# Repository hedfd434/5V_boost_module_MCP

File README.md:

# 5V converter evaluation board (MCP1640T-I/CHY)
this board allows user to get 5V power supply with maximum out current of 1A (limited by coil to 0.8A).
You can safely power your 5V devices controlled by MCU's or evaluation boards

<figure>

  <figcaption>
    Image 1 and 2. Board in real usage power 5V servo
  </figcaption>
</figure>

## features
- DC to DC power conversion (boost)
- input voltage 3.0 to 4.2 V (possible change to range of 0.9 to 1.7V by replacing 309ohm resistor with 562ohm resistor)
- up to 95% efficiency in range of 10 - 100mA
- custom enabler: you can control on and off state by EN pin or permanently solder the 0ohm resistor.

<figure>

  <figcaption>
    Image 3 and 4. Detailed view with real scale.
  </figcaption>
</figure>

## issues
- the GPIO pins are not alligned, it requires using 2 bread boards or custom cutouts in pcb.

## components used in the project
1. 5V chip MCP1640T-I/CHY
2. coil LQM21PN4R7MGRD
3. 10uF 0603 capacitor
4. 4.7uG 0603 capacitor
4. 0ohm 0603 resitor
5. 309ohm 0603 resistor
6. 976ohm 0603 resistor

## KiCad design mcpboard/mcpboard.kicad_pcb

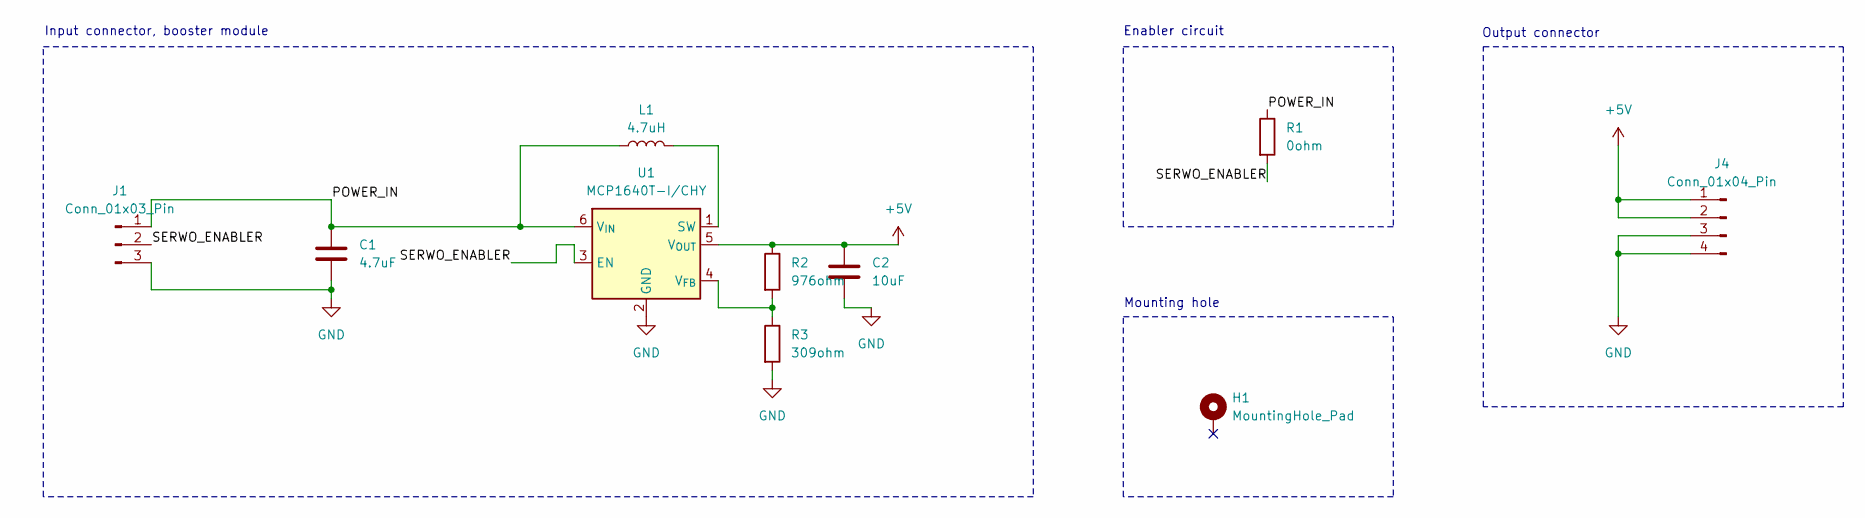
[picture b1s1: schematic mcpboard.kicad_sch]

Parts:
C1: 4.7uF; C_0603_1608Metric
C2: 10uF; C_0603_1608Metric
H1: MountingHole_Pad; MountingHole_2.2mm_M2
J1: Conn_01x03_Pin; PinHeader_1x03_P2.54mm_Vertical
J4: Conn_01x04_Pin; PinHeader_1x04_P2.54mm_Vertical
L1: 4.7uH; L_0805_2012Metric
R1: 0ohm; R_0603_1608Metric
R2: 976ohm; R_0603_1608Metric
R3: 309ohm; R_0603_1608Metric
U1: MCP1640T-I/CHY; SOT-23-6

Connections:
+5V: C2.1, J4.1, J4.2, R2.1, U1.5 (V_{OUT})
/POWER_IN: C1.1, J1.1, L1.1, R1.1, U1.6 (V_{IN})
/SERWO_ENABLER: J1.2, R1.2, U1.3 (EN)
GND: C1.2, C2.2, J1.3, J4.3, J4.4, R3.2, U1.2 (GND)
unnamed: L1.2, U1.1 (SW)
unnamed: R2.2, R3.1, U1.4 (V_{FB})

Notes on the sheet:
Mounting hole
Enabler circuit
Output connector
Input connector, booster module

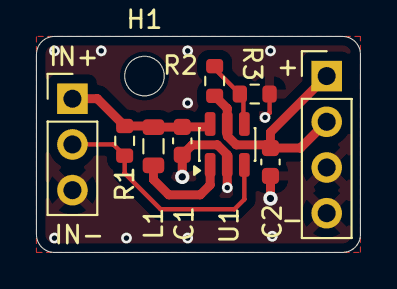
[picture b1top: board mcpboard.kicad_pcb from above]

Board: 2 copper layers, 18.0 x 12.0 mm, 10 parts (0 on the bottom side), 6 nets.

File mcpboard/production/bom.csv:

Designator,Footprint,Quantity,Value,LCSC Part #
C1,0603,1,4.7uF,
C2,0603,1,10uF,
L1,0805,1,4.7uH,
R1,0603,1,0ohm,
R2,0603,1,976ohm,
R3,0603,1,309ohm,
U1,SOT-23-6,1,MCP1640T-I/CHY,
